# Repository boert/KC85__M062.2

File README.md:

# M062.2, Speichermodul für KC85
TTL-Version des Speichermodul M062 für den KC85/3..4..5 mit 32 kByte RAM (nichtflüchtig) oder 64 kByte EPROM

## Motivation
Um die Erweiterung der EPROM-Generator-Software [^1] zu testen, wurde eine passende Hardware benötigt.
Das M062 von E. Müller ist ein Speichermodul für den KC85 aus Mühlhausen, das entweder mit einem EPROM (64 kByte) oder einem nichtflüchtgen SRAM (32 kByte) bestückt werden kann. Durch den Einsatz eines CPLD werden im Original nur vier Schaltkreise benötigt.

Die hier vorgestellte Lösung entstand auf Basis einer Schaltungsbeschreibung in VHDL.

Mit Hilfe von yosys [^2] und dem ghdl-plugin [^3] ist es möglich aus der Schaltungsbeschreibung eine Netzliste zu erzeugen, die Elemente aus einer bereitgestellten TTL-Bibliothek verwendet.

<p align="center">
  
&nbsp;
  
</p>

Diese Netzliste wurde als Basis für den Schaltplan herangezogen.
Inklusive Speicher werden nun elf Schaltkreise benötigt.

Änderungen gegenüber dem Original
- Einsatz diskreter TTL-Schaltkreise statt CPLD
- Unterstützung für Schreibschutzbit W im Steuerbyte
- Strukturbyte zwischen F3h und 01h (Autostart) umschaltbar

Übernommen wurde die Idee mit der kleinen Zusatzplatine für die Segmentanzeige.

## Nutzung
Das Steuerbyte ist wie folgt aufgebaut:

Bit       | 7 | 6 | 5 | 4 | 3 | 2 | 1 | 0
--------- | - | - | - | - | - | - | - | -
Bedeutung | A | A | A | S | S | S | W | M

Das Speichermodul kann aus dem System CAOS mit dem Befehl SWITCH geschaltet werden.

Bit 7 | Bit 6 | Bit 5 | Adressauswahl A
----- | ----- | ----- | ---------------
0 | 0 | 0 | 0000h
0 | 0 | 1 | 2000h
0 | 1 | 0 | 4000h
0 | 1 | 1 | 6000h
1 | 0 | 0 | 8000h
1 | 0 | 1 | A000h
1 | 1 | 0 | C000h
1 | 1 | 1 | E000h

Bit 4 | Bit 3 | Bit 2 | Segment S
----- | ----- | ----- | ---------
0 | 0 | 0 | 0
0 | 0 | 1 | 1
0 | 1 | 0 | 2
0 | 1 | 1 | 3
1 | 0 | 0 | 4
1 | 0 | 1 | 5
1 | 1 | 0 | 6
1 | 1 | 1 | 7

Die Segmente 4 bis 7 existieren nur bei Bestückung mit 64 kByte EPROM.

Bit 1 | Schreibschutz W
----- | ------
0 | aktiv (read only)
1 | inaktiv (read write)

Bit 0 | Modulzustand M
----- | ------
0 | inaktiv
1 | aktiv

### Beispiel
Angenommen das Modul M062.2 steckt im Modulschacht 0C. 

Um das Segement 3 im Speicher auf Adresse 4000h im Modus Schreiben/Lesen zu aktivieren, wird der CAOS-Befehl "SWITCH C 4F" verwendet. 

Um das Segement 7 im Speicher auf Adresse C000h im Modul Nur-Lesen zu aktivieren, wird der CAOS-Befehl "SWITCH C DD" verwendet.

## Links
[^1]: https://github.com/boert/KC85__M037_segmented_ROM/tree/main/EPROM-Generator
[^2]: https://yosyshq.net/yosys/
[^3]: https://github.com/ghdl/ghdl-yosys-plugin

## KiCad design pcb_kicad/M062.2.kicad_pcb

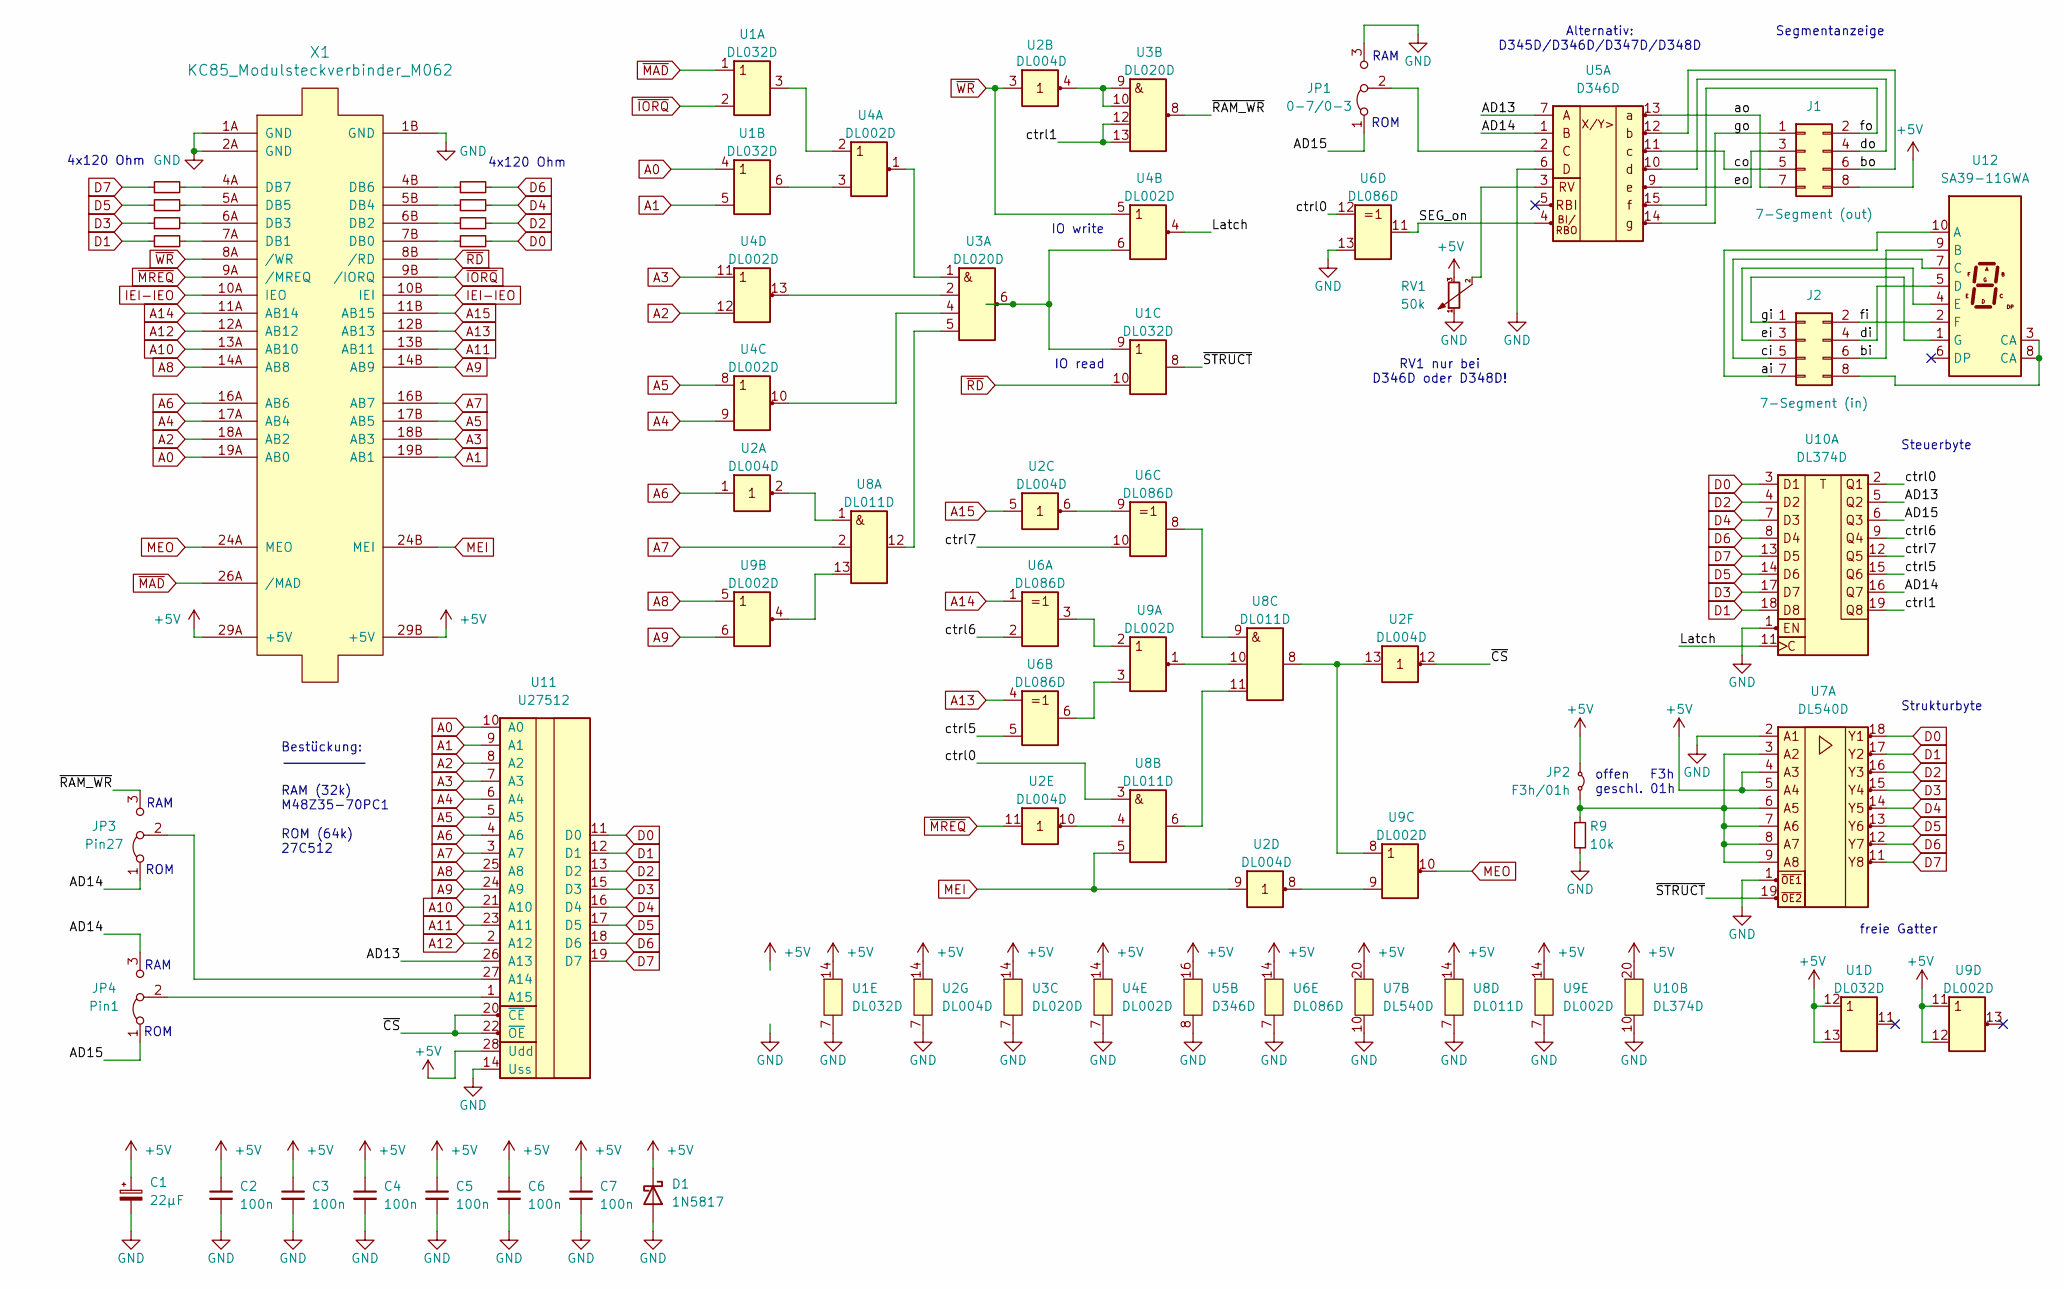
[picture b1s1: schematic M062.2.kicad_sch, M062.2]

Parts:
C1: 22µF; CP_Axial_L18.0mm_D8.0mm_P25.00mm_Horizontal
C2, C3, C4, C5, C6, C7: 100n; C_Rect_L7.0mm_W2.0mm_P5.00mm
D1: 1N5817; D_DO-41_SOD81_P10.16mm_Horizontal
J1: 7-Segment (out); PinSocket_2x04_P2.54mm_Horizontal
J2: 7-Segment (in); PinHeader_2x04_P2.54mm_Vertical
JP1: 0-7/0-3; PinHeader_1x03_P2.54mm_Vertical
JP2: F3h/01h; PinHeader_1x02_P2.54mm_Vertical
JP3: Pin27; PinHeader_1x03_P2.54mm_Vertical
JP4: Pin1; PinHeader_1x03_P2.54mm_Vertical
R1, R2, R3, R4, R5, R6, R7, R8: 120; R_Axial_DIN0309_L9.0mm_D3.2mm_P15.24mm_Horizontal
R9: 10k; R_Axial_DIN0309_L9.0mm_D3.2mm_P15.24mm_Horizontal
RV1: 50k; Potentiometer_ACP_CA9-V10_Vertical
U1: DL032D; DIP-14_W7.62mm_LongPads
U2: DL004D; DIP-14_W7.62mm_LongPads
U3: DL020D; DIP-14_W7.62mm_LongPads
U4, U9: DL002D; DIP-14_W7.62mm_LongPads
U5: D346D; DIP-16_W7.62mm_LongPads
U6: DL086D; DIP-14_W7.62mm_LongPads
U7: DL540D; DIP-20_W7.62mm_LongPads
U8: DL011D; DIP-14_W7.62mm_LongPads
U10: DL374D; DIP-20_W7.62mm_LongPads
U11: U27512; DIP-28_W15.24mm_Socket_LongPads
U12: SA39-11GWA; Sx39-1xxxxx
X1: KC85_Modulsteckverbinder_M062; KC85_Modul_M062

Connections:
+5V: C1.1, C2.1, C3.1, C4.1, C5.1, C6.1, C7.1, D1.1 (K), J1.8, JP2.2 (B), RV1.3, U1.12 (A4), U1.13 (B4), U1.14 (Vcc), U2.14 (Vcc), U3.14 (Vcc), U4.14 (Vcc), U5.16 (Vcc), U6.14 (Vcc), U7.4 (A3), U7.5 (A4), U7.20 (Vcc), U8.14 (Vcc), U9.11 (A4), U9.12 (B4), U9.14 (Vcc), U10.20 (Vcc), U11.28 (Udd), X1.29A (+5V), X1.29B (+5V)
/AD13: U5.7 (A), U10.5 (Q2), U11.26 (A13)
/AD14: JP3.1 (A), JP4.3 (B), U5.1 (B), U10.16 (Q7)
/AD15: JP1.1 (A), JP4.1 (A), U10.6 (Q3)
/Latch: U4.4 (Y2), U10.11 (C)
/SEG_on: U5.4 (BI/RBO), U6.11 (Y4)
/ai: J2.7, U12.10 (A)
/ao: J1.7, U5.13 (a)
/bi: J2.6, U12.9 (B)
/bo: J1.6, U5.12 (b)
/ci: J2.5, U12.7 (C)
/co: J1.5, U5.11 (c)
/ctrl0: U6.12 (A4), U8.3 (A2), U10.2 (Q1)
/ctrl1: U3.12 (C2), U3.13 (D2), U10.19 (Q8)
/ctrl5: U6.5 (B2), U10.15 (Q6)
/ctrl6: U6.2 (B1), U10.9 (Q4)
/ctrl7: U6.10 (B3), U10.12 (Q5)
/di: J2.4, U12.5 (D)
/do: J1.4, U5.10 (d)
/ei: J2.3, U12.4 (E)
/eo: J1.3, U5.9 (e)
/fi: J2.2, U12.2 (F)
/fo: J1.2, U5.15 (f)
/gi: J2.1, U12.1 (G)
/go: J1.1, U5.14 (g)
/~CS: U2.12 (Y6), U11.20 (~CE), U11.22 (~OE)
/~RAM_WR: JP3.3 (B), U3.8 (Y2)
/~STRUCT: U1.8 (Y3), U7.19 (~OE2)
A0: U1.4 (A2), U11.10 (A0), X1.19A (AB0)
A1: U1.5 (B2), U11.9 (A1), X1.19B (AB1)
A2: U4.12 (B4), U11.8 (A2), X1.18A (AB2)
A3: U4.11 (A4), U11.7 (A3), X1.18B (AB3)
A4: U4.9 (B3), U11.6 (A4), X1.17A (AB4)
A5: U4.8 (A3), U11.5 (A5), X1.17B (AB5)
A6: U2.1 (A1), U11.4 (A6), X1.16A (AB6)
A7: U8.2 (B1), U11.3 (A7), X1.16B (AB7)
A8: U9.5 (A2), U11.25 (A8), X1.14A (AB8)
A9: U9.6 (B2), U11.24 (A9), X1.14B (AB9)
A10: U11.21 (A10), X1.13A (AB10)
A11: U11.23 (A11), X1.13B (AB11)
A12: U11.2 (A12), X1.12A (AB12)
A13: U6.4 (A2), X1.12B (AB13)
A14: U6.1 (A1), X1.11A (AB14)
A15: U2.5 (A3), X1.11B (AB15)
D0: R8.2, U7.18 (Y1), U10.3 (D1), U11.11 (D0)
D1: R7.1, U7.17 (Y2), U10.18 (D8), U11.12 (D1)
D2: R6.2, U7.16 (Y3), U10.4 (D2), U11.13 (D2)
D3: R5.1, U7.15 (A4), U10.17 (D7), U11.15 (D3)
D4: R4.2, U7.14 (Y5), U10.7 (D3), U11.16 (D4)
D5: R3.1, U7.13 (Y6), U10.14 (D6), U11.17 (D5)
D6: R2.2, U7.12 (Y7), U10.8 (D4), U11.18 (D6)
D7: R1.1, U7.11 (Y8), U10.13 (D5), U11.19 (D7)
GND: C1.2, C2.2, C3.2, C4.2, C5.2, C6.2, C7.2, D1.2 (A), JP1.3 (B), R9.2, RV1.1, U1.7 (GND), U2.7 (GND), U3.7 (GND), U4.7 (GND), U5.6 (D), U5.8 (GND), U6.7 (GND), U6.13 (B4), U7.1 (~OE1), U7.2 (A1), U7.10 (GND), U8.7 (GND), U9.7 (GND), U10.1 (EN), U10.10 (GND), U11.14 (Uss), X1.1A (GND), X1.1B (GND), X1.2A (GND)
IEI-IEO: X1.10A (IEO), X1.10B (IEI)
MEI: U2.9 (A4), U8.5 (C2), X1.24B (MEI)
MEO: U9.10 (Y3), X1.24A (MEO)
unnamed: J2.8, U12.3 (CA), U12.8 (CA)
unnamed: JP1.2 (C), U5.2 (C)
unnamed: JP2.1 (A), R9.1, U7.3 (A2), U7.6 (A5), U7.7 (A6), U7.8 (A7), U7.9 (A8)
unnamed: JP3.2 (C), U11.27 (A14)
unnamed: JP4.2 (C), U11.1 (A15)
unnamed: U1.3 (Y1), U4.2 (A1)
unnamed: U1.6 (Y2), U4.3 (B1)
unnamed: U1.9 (A3), U3.6 (Y1), U4.6 (B2)
unnamed: U2.2 (Y1), U8.1 (A1)
unnamed: U2.4 (Y2), U3.9 (A2), U3.10 (B2)
unnamed: U2.6 (Y3), U6.9 (A3)
unnamed: U2.8 (Y4), U9.9 (B3)
unnamed: U2.10 (Y5), U8.4 (B2)
unnamed: U2.13 (A6), U8.8 (Y3), U9.8 (A3)
unnamed: U3.1 (A1), U4.1 (Y1)
unnamed: U3.2 (B1), U4.13 (Y4)
unnamed: U3.4 (C1), U4.10 (Y3)
unnamed: U3.5 (D1), U8.12 (Y1)
unnamed: RV1.2, U5.3 (RV)
unnamed: U6.3 (Y1), U9.2 (A1)
unnamed: U6.6 (Y2), U9.3 (B1)
unnamed: U6.8 (Y3), U8.9 (A3)
unnamed: U8.13 (C1), U9.4 (Y2)
unnamed: U8.6 (Y2), U8.11 (C3)
unnamed: U8.10 (B3), U9.1 (Y1)
unnamed: R8.1, X1.7B (DB0)
unnamed: R7.2, X1.7A (DB1)
unnamed: R6.1, X1.6B (DB2)
unnamed: R5.2, X1.6A (DB3)
unnamed: R4.1, X1.5B (DB4)
unnamed: R3.2, X1.5A (DB5)
unnamed: R2.1, X1.4B (DB6)
unnamed: R1.2, X1.4A (DB7)
~IORQ: U1.2 (B1), X1.9B (/IORQ)
~MAD: U1.1 (A1), X1.26A (/MAD)
~MREQ: U2.11 (A5), X1.9A (/MREQ)
~RD: U1.10 (B3), X1.8B (/RD)
~WR: U2.3 (A2), U4.5 (A2), X1.8A (/WR)

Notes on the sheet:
Steuerbyte
ROM
4x120 Ohm
IO read
IO write
Strukturbyte
RV1 nur bei D346D oder D348D!
RAM
freie Gatter
Bestückung: RAM (32k) M48Z35-70PC1 ROM (64k) 27C512
offen F3h geschl. 01h
Segmentanzeige
Alternativ: D345D/D346D/D347D/D348D

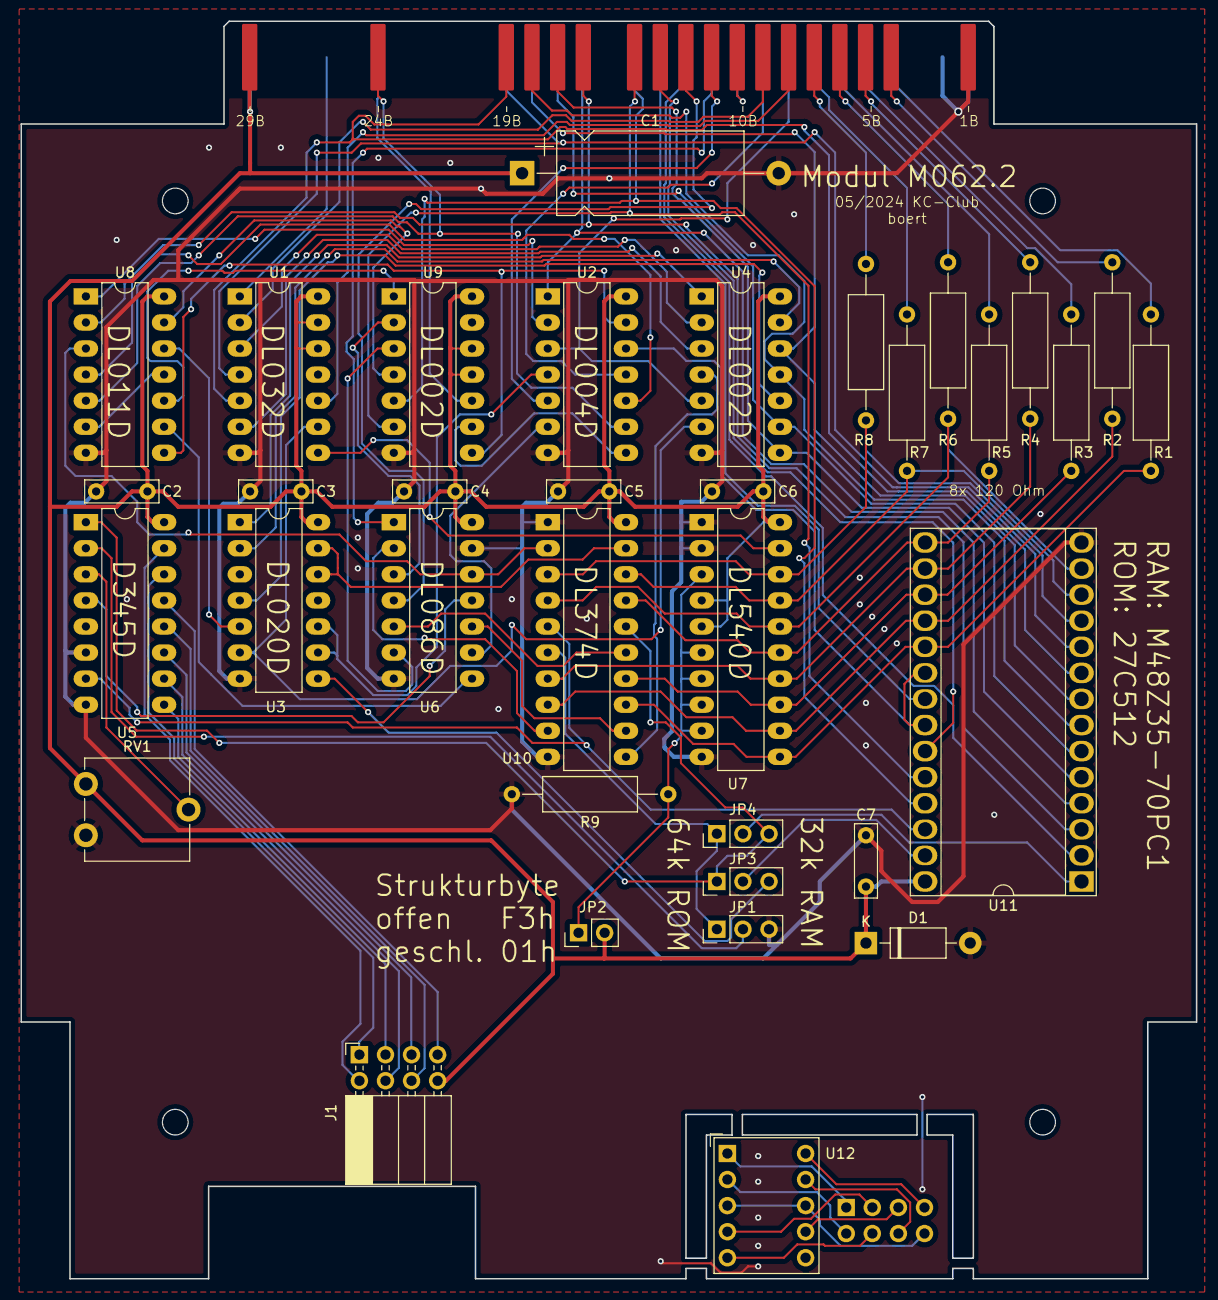
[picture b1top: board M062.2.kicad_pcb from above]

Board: 2 copper layers, 114.5 x 122.5 mm, 37 parts (1 on the bottom side), 94 nets.

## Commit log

2024-05-12 add: lots of files
2024-05-14 change: Bohrungen für Speicherchip vergößert
2024-05-14 add: Rand
2024-05-15 add: Tool FILLM062
2024-05-15 add: EPROM Images
2024-06-20 add: readme
2024-06-20 add: Frontblende
